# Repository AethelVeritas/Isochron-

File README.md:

# Isochron
A PCB badge that has a piezo buzzer and an OLED, making it usable as a metronome! It also has two capacitive touch buttons, with one upping the BPM and the other generating a random BPM. "Isochron" is derived from "_isochronos"_, meaning "equal time" in Greek.

## Pictures

## BOM
| Part Name | Quantity | Part Price | Link |
|---|---|---|---|
| CR2032-BS-6-1 (Battery Holder) | 1 | $0.1380 | https://www.lcsc.com/product-detail/C70377.html |
| ATTINY1614-SSN (Microcontroller) | 1 | $2.5972 | https://www.lcsc.com/product-detail/C614832.html |
| PKLCS1212E4001-R1 (Buzzer) | 1 | $1.3338 | https://www.lcsc.com/product-detail/C113159.html |
| B3U-1000P (Tactile Switch) | 1 | $0.1783 | https://www.lcsc.com/product-detail/C231329.html |
|128x64 OLED | 1 | $2 | Owned | |
|0603 100 oHm resistor| 2 | ? | Electronics market

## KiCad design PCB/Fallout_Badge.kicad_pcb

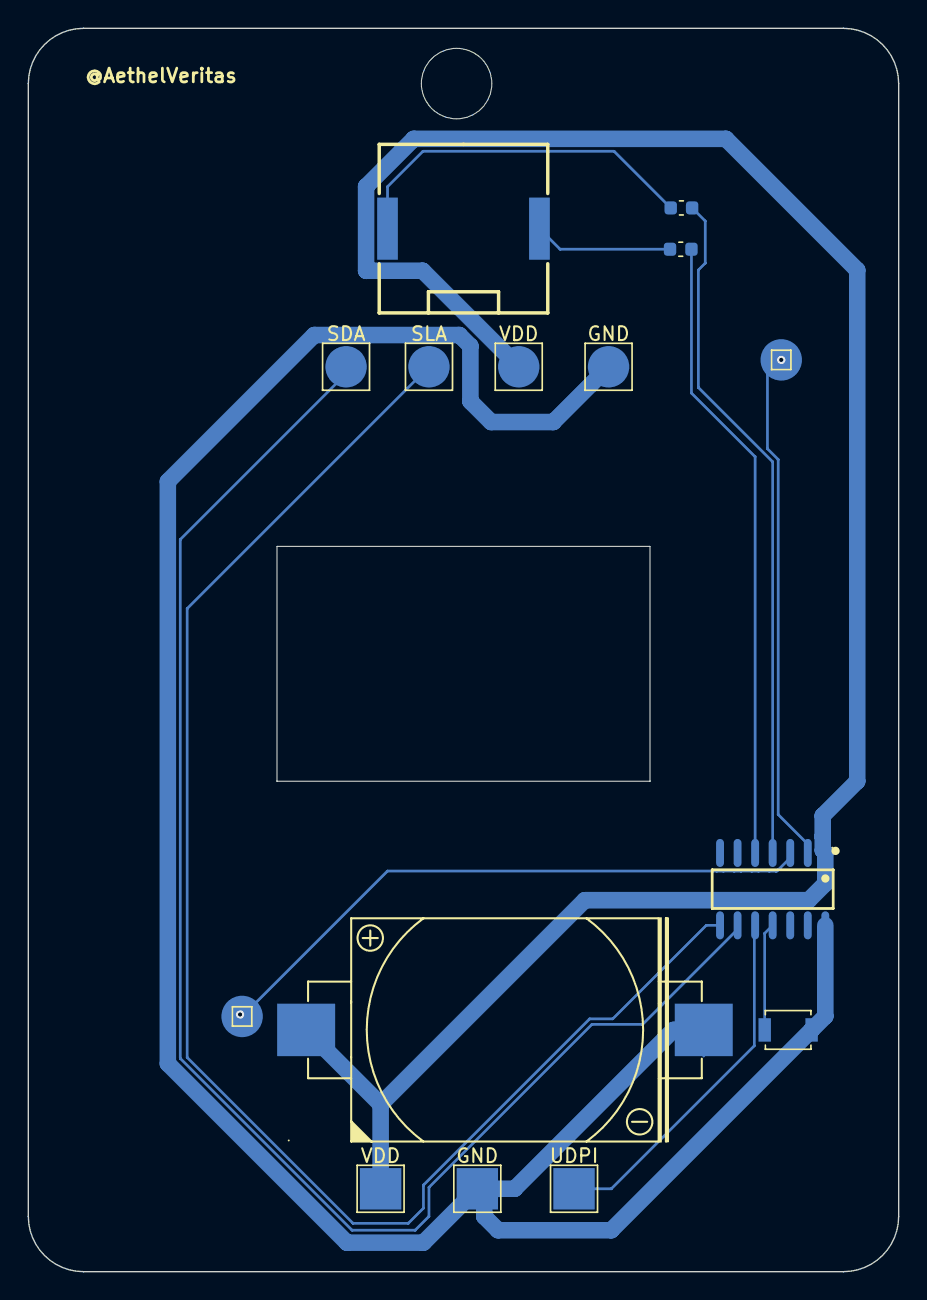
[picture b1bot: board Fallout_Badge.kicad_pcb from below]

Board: 2 copper layers, 63.0 x 90.0 mm, 15 parts (15 on the bottom side), 11 nets.

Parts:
B1: CR2032-BS-6-1; BAT-TH_CR2032-BS-6-1
BUZZER: PKLCS1212E4001-R1; BUZ-SMD_2P-L12.0-W12.0-L_PKLCS1212E4001-R1
GND: TestPoint; TestPoint_Pad_3.0x3.0mm
GND#2: TestPoint; TestPoint_Pad_3.0x3.0mm
R1, R2: 47; C_0603_1608Metric
SDA: TestPoint; TestPoint_Pad_3.0x3.0mm
SLA: TestPoint; TestPoint_Pad_3.0x3.0mm
SW2: SW_SPST; SW_SPST_B3U-1000P
TP9: TestPoint; TestPoint_Pad_1.0x1.0mm
Touch_1: TestPoint; TestPoint_Pad_1.0x1.0mm
U1: ATTINY1614-SSN_C614832; SOIC-14_L8.7-W3.9-P1.27-LS6.0-BL
UDPI: TestPoint; TestPoint_Pad_3.0x3.0mm
VDD: TestPoint; TestPoint_Pad_3.0x3.0mm
VDD#2: TestPoint; TestPoint_Pad_3.0x3.0mm

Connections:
Button: SW2.1 (A), U1.11 (PA1)
GND: B1.2, GND.1 (1_1), GND#2.1 (1_1), SW2.2 (B), U1.14 (GND)
unnamed: BUZZER.1 (+), R2.2
unnamed: BUZZER.2 (-), R1.1
unnamed: Touch_1.1 (1_1), U1.2 (PA4)
unnamed: TP9.1 (1_1), U1.3 (PA5)
Piezo1: R2.1, U1.4 (PA6)
Piezo2: R1.2, U1.5 (PA7)
SLA: SDA.1 (1_1), U1.9 (PB0)
UDPI: U1.10 (PA0/#RESET/UPDI), UDPI.1 (1_1)
VDD: B1.1, U1.1 (VDD), VDD.1 (1_1), VDD#2.1 (1_1)
